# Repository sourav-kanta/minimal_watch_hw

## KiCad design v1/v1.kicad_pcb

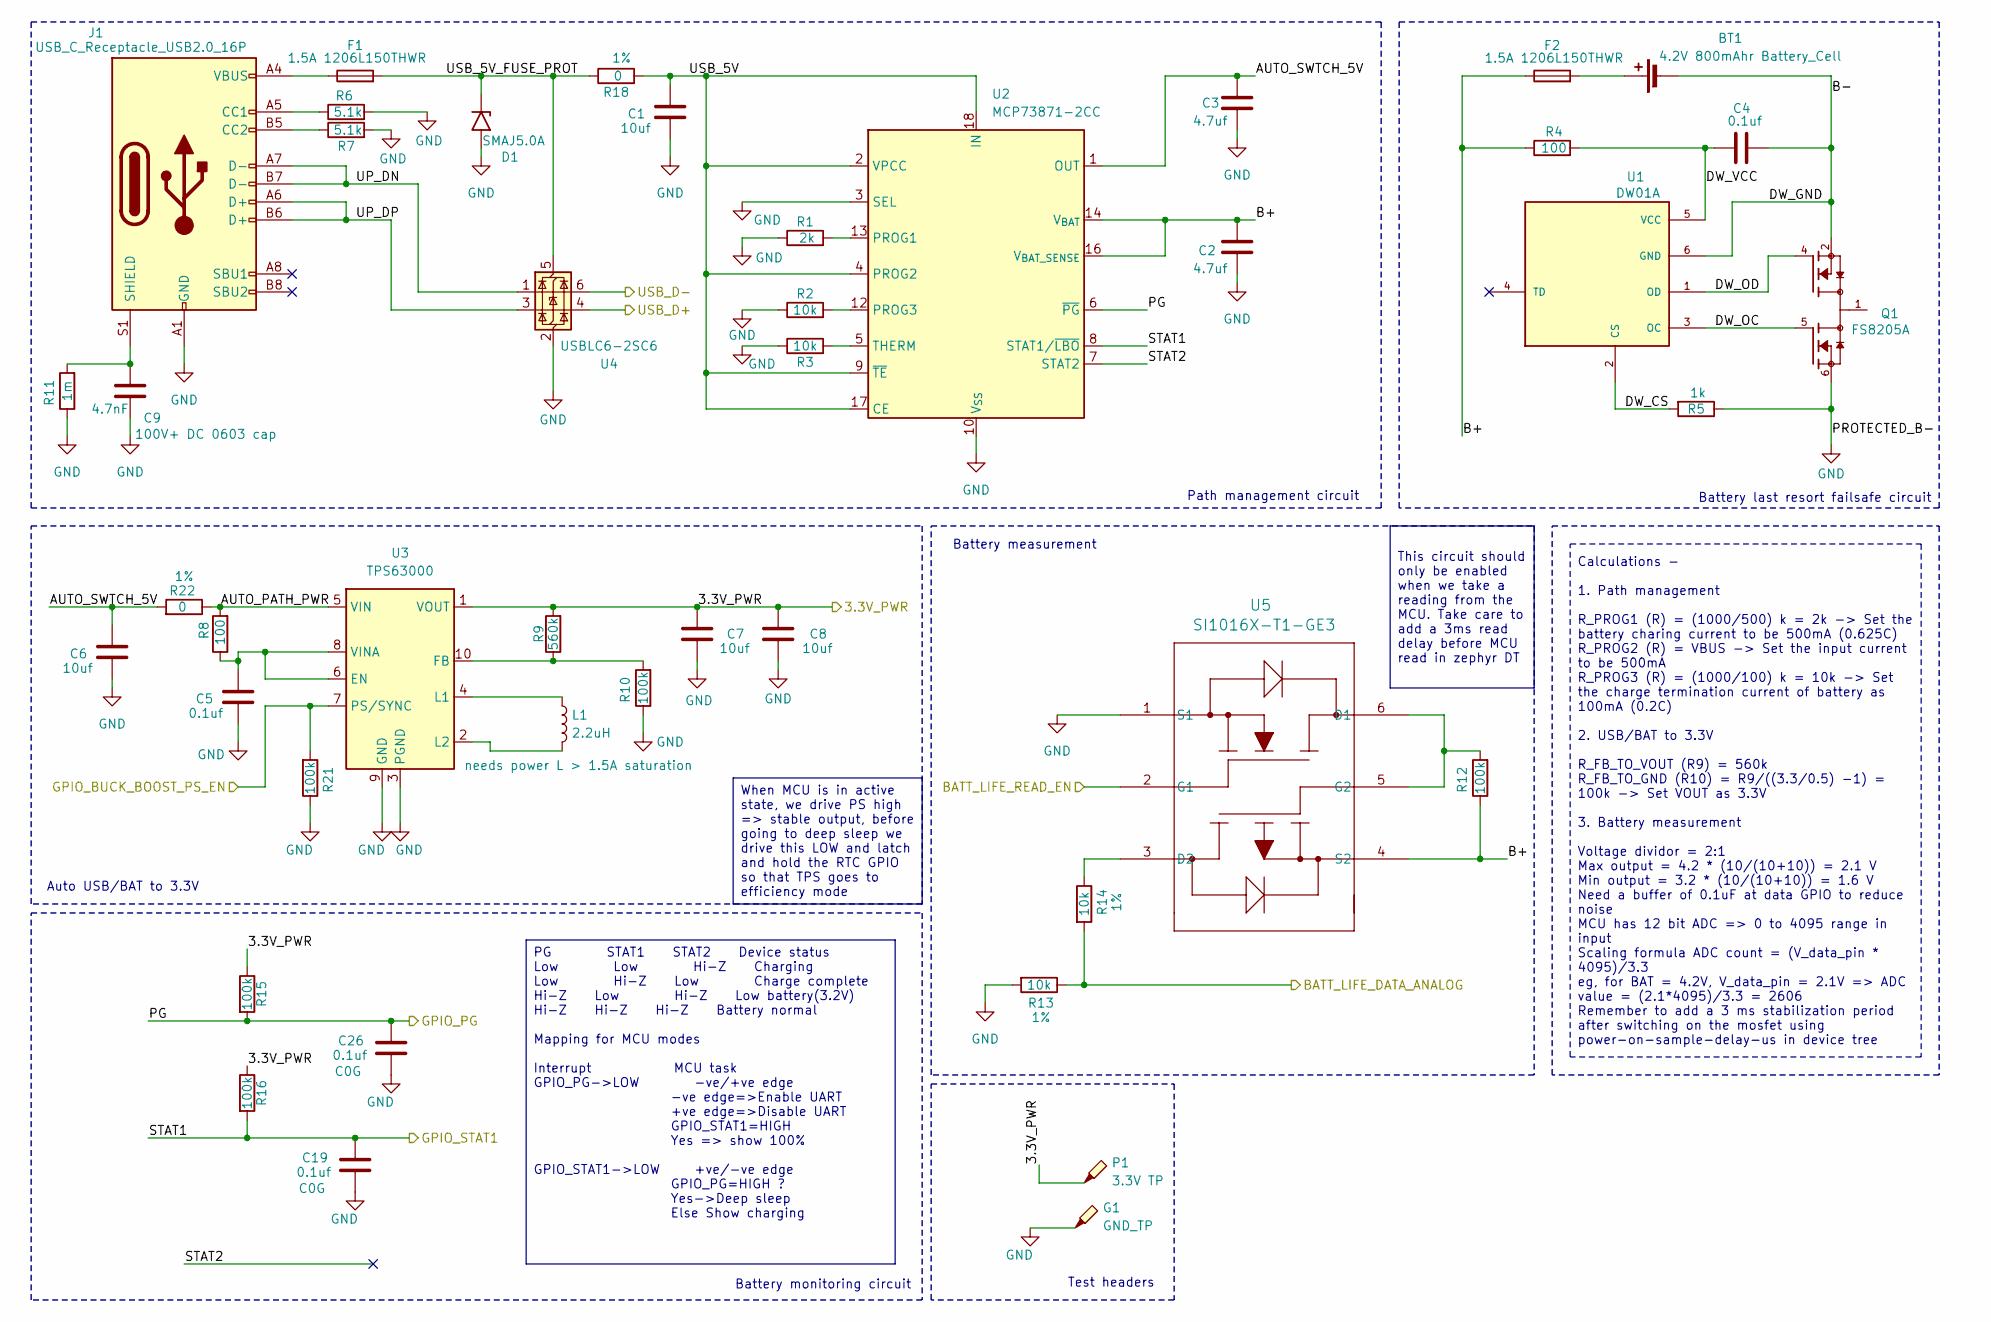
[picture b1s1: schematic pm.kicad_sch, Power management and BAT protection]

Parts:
BT1: 4.2V 800mAhr Battery_Cell; 4.2v_battery_mount
C1, C6, C7, C8: 10uf; C_0603_1608Metric
C2, C3: 4.7uf; C_0603_1608Metric
C4, C5: 0.1uf; C_0603_1608Metric
C9: 4.7nF; C_1210_3225Metric_Pad1.33x2.70mm_HandSolder
C19, C26: 0.1uf; C_0402_1005Metric_Pad0.74x0.62mm_HandSolder
D1: SMAJ5.0A; D_SMA
F1, F2: 1.5A 1206L150THWR; Fuse_1206_3216Metric
G1: GND_TP; TestPoint_Pad_D2.5mm
J1: USB_C_Receptacle_USB2.0_16P; USB_C_Receptacle_HRO_TYPE-C-31-M-12
L1: 2.2uH; L_Sunlord_SWPA4030S
P1: 3.3V TP; TestPoint_Pad_D2.5mm
Q1: FS8205A; SOP65P640X120-8N; PARTREV 1.7
R1: 2k; R_0603_1608Metric_Pad0.98x0.95mm_HandSolder
R2, R3, R13, R14: 10k; R_0603_1608Metric_Pad0.98x0.95mm_HandSolder
R4, R8: 100; R_0603_1608Metric_Pad0.98x0.95mm_HandSolder
R5: 1k; R_0603_1608Metric_Pad0.98x0.95mm_HandSolder
R6, R7: 5.1k; R_0603_1608Metric_Pad0.98x0.95mm_HandSolder
R9: 560k; R_0603_1608Metric_Pad0.98x0.95mm_HandSolder
R10, R12, R15, R16, R21: 100k; R_0603_1608Metric_Pad0.98x0.95mm_HandSolder
R11: 1m; R_0603_1608Metric_Pad0.98x0.95mm_HandSolder
R18, R22: 0; R_0603_1608Metric_Pad0.98x0.95mm_HandSolder
U1: DW01A; SOT95P280X145-6N; PARTREV 1.8
U2: MCP73871-2CC; QFN-20-1EP_4x4mm_P0.5mm_EP2.5x2.5mm
U3: TPS63000; Texas_DRC0010J_ThermalVias
U4: USBLC6-2SC6; SOT-23-6
U5: SI1016X-T1-GE3; SOT_X-T1-GE3_VIS-M

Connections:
/MCU/BATT_READ_DATA_ANALOG: R13.1, R14.2; also elsewhere on the board
/MCU/BAT_READ_ENABLE: U5.2 (G1); also elsewhere on the board
/MCU/PROTECTED_USB_D+: U4.4 (I/O2); also elsewhere on the board
/MCU/PROTECTED_USB_D-: U4.6 (I/O1); also elsewhere on the board
/MCU/PWR_EFFICIENCY_MODE: R21.2, U3.7 (PS/SYNC); also elsewhere on the board
/Power Module/3.3V_PWR: C7.1, C8.1, P1.1, R9.2, R15.1, R16.1, U3.1 (VOUT); also elsewhere on the board
/Power Module/AUTO_PATH_PWR: R8.2, R22.1, U3.5 (VIN)
/Power Module/AUTO_SWTCH_5V: C3.1, C6.1, R22.2, U2.1 (OUT), U2.20 (OUT)
/Power Module/B+: C2.1, F2.1, R4.1, R12.1, U2.14 (V_{BAT}), U2.15 (V_{BAT}), U2.16 (V_{BAT_SENSE}), U5.4 (S2)
/Power Module/B-: BT1.1 (-), C4.1, Q1.2, Q1.3, U1.6 (GND)
/Power Module/DW_CS: R5.2, U1.2 (CS)
/Power Module/DW_OC: Q1.5, U1.3 (OC)
/Power Module/DW_OD: Q1.4, U1.1 (OD)
/Power Module/DW_VCC: C4.2, R4.2, U1.5 (VCC)
/Power Module/PG: C26.1, R15.2, U2.6 (~PG); also elsewhere on the board
/Power Module/STAT1: C19.1, R16.2, U2.8 (STAT1/~LBO); also elsewhere on the board
/Power Module/STAT2: U2.7 (STAT2)
/Power Module/UP_DN: J1.A7 (D-), J1.B7 (D-), U4.1 (I/O1)
/Power Module/UP_DP: J1.A6 (D+), J1.B6 (D+), U4.3 (I/O2)
/Power Module/USB_5V: C1.1, R18.2, U2.2 (VPCC), U2.4 (PROG2), U2.9 (~TE), U2.17 (CE), U2.18 (IN), U2.19 (IN)
/Power Module/USB_5V_FUSE_PROT: D1.1 (A1), F1.2, R18.1, U4.5 (VBUS)
GND: C1.2, C2.2, C3.2, C5.2, C6.2, C7.2, C8.2, C9.2, C19.2, C26.2, D1.2 (A2), G1.1, J1.A1 (GND), J1.A12 (GND), J1.B1 (GND), J1.B12 (GND), Q1.6, Q1.7, R1.1, R2.1, R3.1, R5.1, R6.2, R7.2, R10.1, R11.1, R13.2, R21.1, U2.3 (SEL), U2.10 (V_{SS}), U2.11 (V_{SS}), U2.21 (V_{SS}), U3.3 (PGND), U3.9 (GND), U3.11 (PGND), U4.2 (GND), U5.1 (S1); also elsewhere on the board
unnamed: BT1.2 (+), F2.2
unnamed: F1.1, J1.A4 (VBUS), J1.A9 (VBUS), J1.B4 (VBUS), J1.B9 (VBUS)
unnamed: J1.A5 (CC1), R6.1
unnamed: J1.B5 (CC2), R7.1
unnamed: C9.1, J1.S1 (SHIELD), R11.2
unnamed: Q1.1, Q1.8
unnamed: R1.2, U2.13 (PROG1)
unnamed: R2.2, U2.12 (PROG3)
unnamed: R3.2, U2.5 (THERM)
unnamed: C5.1, R8.1, U3.6 (EN), U3.8 (VINA)
unnamed: R9.1, R10.2, U3.10 (FB)
unnamed: L1.1, U3.4 (L1)
unnamed: L1.2, U3.2 (L2)
unnamed: R12.2, U5.5 (G2), U5.6 (D1)
unnamed: R14.1, U5.3 (D2)

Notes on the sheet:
Path management circuit
Battery measurement
Test headers
Battery last resort failsafe circuit
Battery monitoring circuit
Auto USB/BAT to 3.3V
PG STAT1 STAT2 Device status Low Low Hi-Z Charging Low Hi-Z Low Charge complete Hi-Z Low Hi-Z Low battery(3.2V) Hi-Z Hi-Z Hi-Z Battery normal Mapping for MCU modes Interrupt MCU task GPIO_PG->LOW -ve/+ve edge -ve edge=>Enable UART +ve edge=>Disable UART GPIO_STAT1=HIGH Yes => show 100% GPIO_STAT1->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
Calculations - 1. Path management R_PROG1 (R) = (1000/500) k = 2k -> Set the battery charing current to be 500mA (0.625C) R_PROG2 (R) = VBUS -> Set the input current to be 500mA R_PROG3 (R) = (1000/100) k = 10k -> Set the charge termination current of battery as 100mA (0.2C) 2. USB/BAT to 3.3V R_FB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
When MCU is in active state, we drive PS high => stable output, before going to deep sleep we drive this LOW and latch and hold the RTC GPIO so that TPS goes to efficiency mode
This circuit should only be enabled when we take a reading from the MCU. Take care to add a 3ms read delay before MCU read in zephyr DT

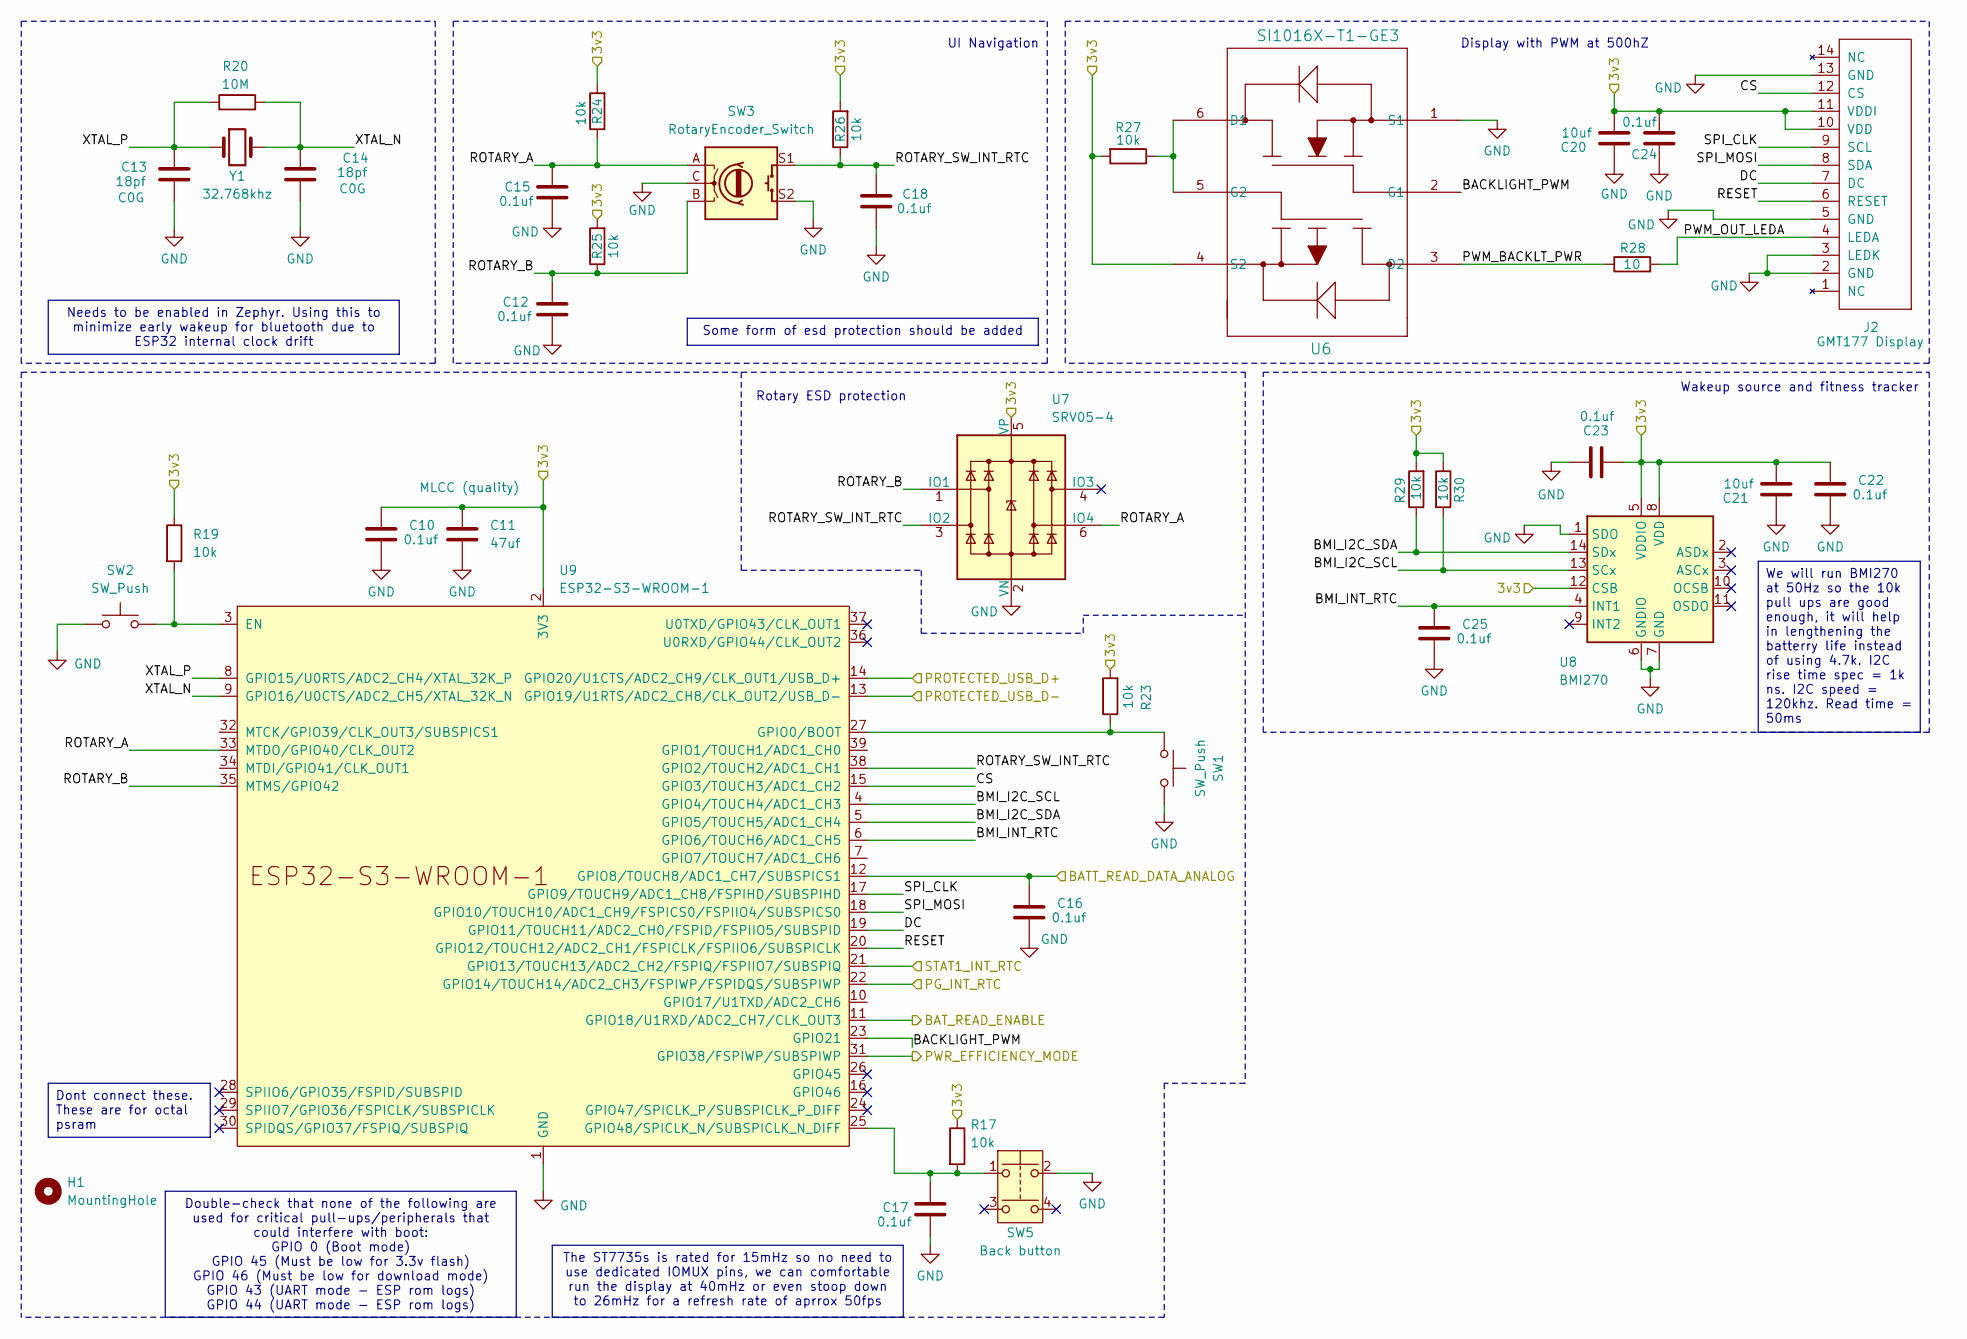
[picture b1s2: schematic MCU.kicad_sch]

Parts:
C10, C12, C15, C16, C17, C18, C22, C23, C24, C25: 0.1uf; C_0603_1608Metric_Pad1.08x0.95mm_HandSolder
C11: 47uf; C_1210_3225Metric_Pad1.33x2.70mm_HandSolder
C13, C14: 18pf; C_0402_1005Metric_Pad0.74x0.62mm_HandSolder
C20, C21: 10uf; C_0603_1608Metric_Pad1.08x0.95mm_HandSolder
H1: MountingHole; MountingHole_3.2mm_M3_ISO14580
J2: GMT177 Display; TE_1-1734839-3_1x13-1MP_P0.5mm_Horizontal
R17, R19, R23, R24, R25, R26, R27, R29, R30: 10k; R_0603_1608Metric_Pad0.98x0.95mm_HandSolder
R20: 10M; R_0603_1608Metric_Pad0.98x0.95mm_HandSolder
R28: 10; R_0603_1608Metric_Pad0.98x0.95mm_HandSolder
SW1, SW2: SW_Push; SW_SPST_B3U-1000P
SW3: RotaryEncoder_Switch; RotaryEncoder_Bourns_Horizontal_PEC12R-2x17F-Sxxxx
SW5: Back button; EVQPUC02K
U6: SI1016X-T1-GE3; SOT_X-T1-GE3_VIS-M
U7: SRV05-4; SOT-23-6
U8: BMI270; Bosch_LGA-14_3x2.5mm_P0.5mm
U9: ESP32-S3-WROOM-1
Y1: 32.768khz; Crystal_SMD_3215-2Pin_3.2x1.5mm

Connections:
/MCU/BACKLIGHT_PWM: U6.2 (G1), U9.23 (GPIO21)
/MCU/BATT_READ_DATA_ANALOG: C16.1, U9.12 (GPIO8/TOUCH8/ADC1_CH7/SUBSPICS1); also elsewhere on the board
/MCU/BAT_READ_ENABLE: U9.11 (GPIO18/U1RXD/ADC2_CH7/CLK_OUT3); also elsewhere on the board
/MCU/BMI_I2C_SCL: R30.2, U8.13 (SCx), U9.4 (GPIO4/TOUCH4/ADC1_CH3)
/MCU/BMI_I2C_SDA: R29.1, U8.14 (SDx), U9.5 (GPIO5/TOUCH5/ADC1_CH4)
/MCU/BMI_INT_RTC: C25.1, U8.4 (INT1), U9.6 (GPIO6/TOUCH6/ADC1_CH5)
/MCU/CS: J2.12 (CS), U9.15 (GPIO3/TOUCH3/ADC1_CH2)
/MCU/DC: J2.7 (DC), U9.19 (GPIO11/TOUCH11/ADC2_CH0/FSPID/FSPIIO5/S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)
/MCU/PROTECTED_USB_D+: U9.14 (GPIO20/U1CTS/ADC2_CH9/CLK_OUT1/USB_D+); also elsewhere on the board
/MCU/PROTECTED_USB_D-: U9.13 (GPIO19/U1RTS/ADC2_CH8/CLK_OUT2/USB_D-); also elsewhere on the board
/MCU/PWM_BACKLT_PWR: R28.1, U6.3 (D2)
/MCU/PWM_OUT_LEDA: J2.4 (LEDA), R28.2
/MCU/PWR_EFFICIENCY_MODE: U9.31 (GPIO38/FSPIWP/SUBSPIWP); also elsewhere on the board
/MCU/RESET: J2.6 (RESET), U9.20 (GPIO12/TOUCH12/ADC2_CH1/FSPICLK/FSPIIO6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)
/MCU/ROTARY_A: C15.1, R24.1, SW3.A, U7.6 (IO4), U9.33 (MTDO/GPIO40/CLK_OUT2)
/MCU/ROTARY_B: C12.1, R25.1, SW3.B, U7.1 (IO1), U9.35 (MTMS/GPIO42)
/MCU/ROTARY_SW_INT_RTC: C18.1, R26.1, SW3.S1, U7.3 (IO2), U9.38 (GPIO2/TOUCH2/ADC1_CH1)
/MCU/SPI_CLK: J2.9 (SCL), U9.17 (GPIO9/TOUCH9/ADC1_CH8/FSPIHD/SUBSPIHD)
/MCU/SPI_MOSI: J2.8 (SDA), U9.18 (GPIO10/TOUCH10/ADC1_CH9/FSPICS0/FSPIIO4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)
/MCU/XTAL_N: C14.1, R20.2, U9.9 (GPIO16/U0CTS/ADC2_CH5/XTAL_32K_N), Y1.2
/MCU/XTAL_P: C13.1, R20.1, U9.8 (GPIO15/U0RTS/ADC2_CH4/XTAL_32K_P), Y1.1
/Power Module/3.3V_PWR: C10.1, C11.1, C20.2, C21.2, C22.1, C23.2, C24.1, J2.10 (VDD), J2.11 (VDDI), R17.1, R19.1, R23.2, R24.2, R25.2, R26.2, R27.2, R29.2, R30.1, U6.4 (S2), U7.5 (VP), U8.5 (VDDIO), U8.8 (VDD), U8.12 (CSB), U9.2 (3V3); also elsewhere on the board
/Power Module/PG: U9.22 (GPIO14/TOUCH14/ADC2_CH3/FSPIWP/FSPIDQS/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); also elsewhere on the board
/Power Module/STAT1: U9.21 (GPIO13/TOUCH13/ADC2_CH2/FSPIQ/FSPIIO7/S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); also elsewhere on the board
GND: C10.2, C11.2, C12.2, C13.2, C14.2, C15.2, C16.2, C17.2, C18.2, C20.1, C21.1, C22.2, C23.1, C24.2, C25.2, J2.2 (GND), J2.3 (LEDK), J2.5 (GND), J2.13 (GND), SW1.2, SW2.1, SW3.C, SW3.S2, SW5.2, U6.1 (S1), U7.2 (VN), U8.1 (SDO), U8.6 (GNDIO), U8.7 (GND), U9.1 (GND), U9.40 (GND), U9.41 (GND); also elsewhere on the board
unnamed: R27.1, U6.5 (G2), U6.6 (D1)
unnamed: R19.2, SW2.2, U9.3 (EN)
unnamed: R23.1, SW1.1, U9.27 (GPIO0/BOOT)
unnamed: C17.1, R17.2, SW5.1, U9.25 (GPIO48/SPICLK_N/SUBSPICLK_N_DIFF)

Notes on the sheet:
Rotary ESD protection
Wakeup source and fitness tracker
Display with PWM at 500hZ
UI Navigation
Some form of esd protection should be added
We will run BMI270 at 50Hz so the 10k pull ups are good enough, it will help in lengthening the batterry life instead of using 4.7k. I2C rise time spec = 1k ns. I2C speed = 120khz. Read time = 50ms
The ST7735s is rated for 15mHz so no need to use dedicated IOMUX pins, we can comfortable run the display at 40mHz or even stoop down to 26mHz for a refresh rate of aprrox 50fps
Dont connect these. These are for octal psram
Needs to be enabled in Zephyr. Using this to minimize early wakeup for bluetooth due to ESP32 internal clock drift
Double-check that none of the following are used for critical pull-ups/peripherals that could interfere with boot: GPIO 0 (Boot mode) GPIO 45 (Must be low for 3.3v flash) GPIO 46 (Must be low for download mode) GPIO 43 (UART mode - ESP rom logs) GPIO 44 (UART mode - ESP rom logs)

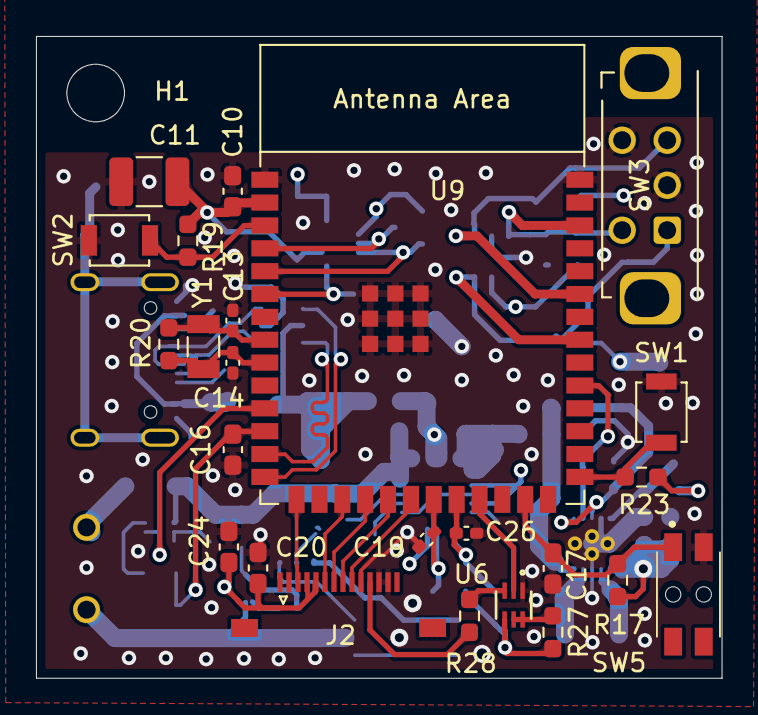
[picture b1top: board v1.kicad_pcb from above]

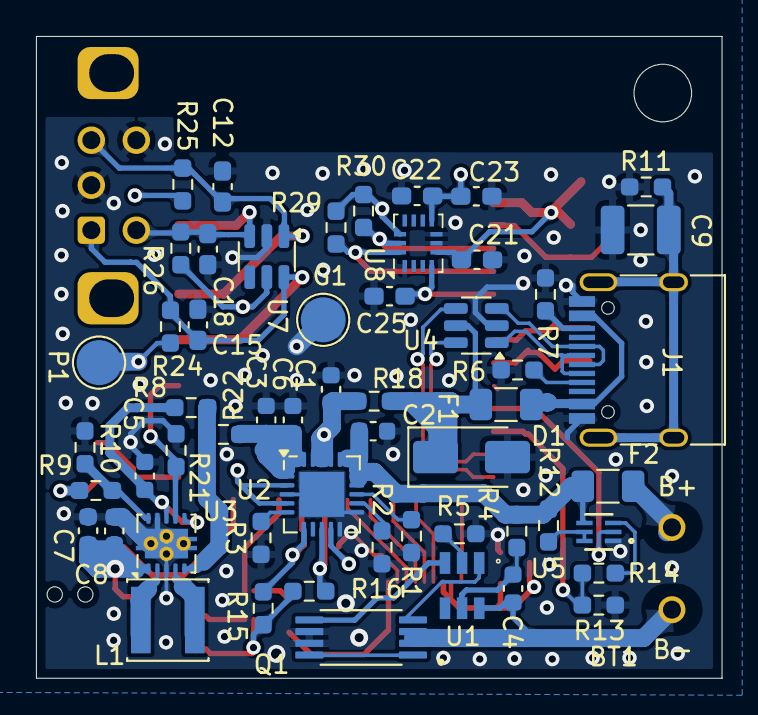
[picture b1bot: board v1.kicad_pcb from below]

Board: 4 copper layers, 38.1 x 35.7 mm, 81 parts (56 on the bottom side), 56 nets.

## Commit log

2026-02-19 Missing files
2026-02-19 Missing files 2.0
2026-03-24 Updated layout
2026-03-24 Updated schematics with relative paths
